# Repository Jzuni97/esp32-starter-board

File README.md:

# esp32-starter-board
A basic project for creating a starter board with an esp32 SoC. 
This is a guide based off of [Robert Feranec's tutorial](https://www.youtube.com/watch?v=S_p0YV-JlfU) on making a custom ESP32 board.

### technical good-to-knows
- [TVS/ESD protection diodes](https://toshiba.semicon-storage.com/info/docget.jsp?did=68869)

### sources
- [espressif devkit docs](https://docs.espressif.com/projects/esp-idf/en/latest/esp32/hw-reference/esp32/get-started-devkitc.html)
- [esp32 datasheet](https://www.espressif.com/sites/default/files/documentation/esp32_datasheet_en.pdf)
- [esp32 devkit schematics](https://dl.espressif.com/dl/schematics/esp32_devkitc_v4_sch.pdf)
- Some components do not exist in standard KiCad library. To use parts available in LCSC or EasyEDA, you can use the following [easyeda-to-kicad converter](https://pypi.org/project/easyeda2kicad/) which relies on LCSC part ids'.

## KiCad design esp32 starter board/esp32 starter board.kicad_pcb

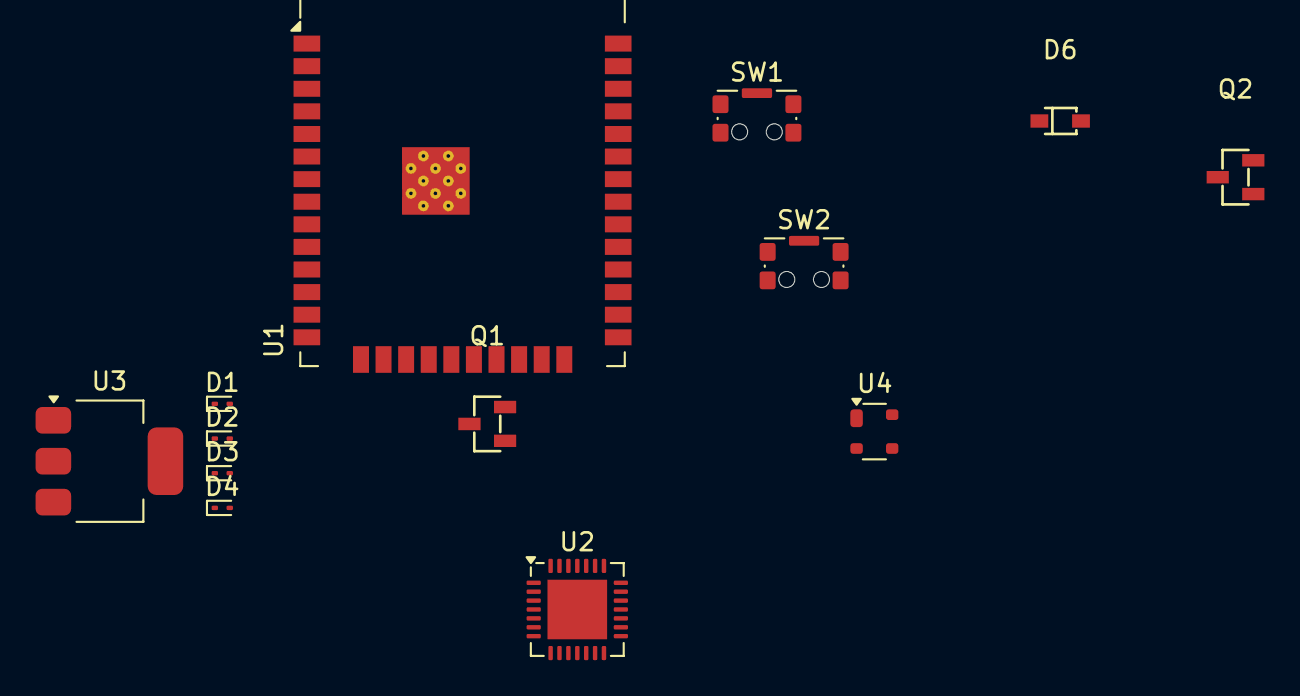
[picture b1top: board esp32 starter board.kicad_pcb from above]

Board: 2 copper layers, 13 parts (0 on the bottom side), 3 nets, no tracks yet.

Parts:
D1, D2, D3, D4: SZESD9B5.0ST5G; D_SOD-923
D6: BAT760-7; SOD-323_L1.8-W1.3-LS2.5-RD
Q1, Q2: SS8050-G; SOT-23-3_L2.9-W1.3-P1.90-LS2.4-BR
SW1, SW2: CK_KMS2xxG; SW_SPST_CK_KMS2xxGP
U1: ESP32-WROOM-32E; ESP32-WROOM-32D
U2: CP2102N-Axx-xQFN28; QFN-28-1EP_5x5mm_P0.5mm_EP3.35x3.35mm
U3: AMS1117-3.3; SOT-223-3_TabPin2
U4: MAX6816; SOT-143

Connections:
+3.3V: U1.2 (VDD), U3.2 (VO)
<NO NET>: U1.1 (GND), U1.15 (GND), U1.38 (GND), U1.39 (GND), U3.1 (GND)
unnamed: U2.3 (GND), U2.29 (GND)
